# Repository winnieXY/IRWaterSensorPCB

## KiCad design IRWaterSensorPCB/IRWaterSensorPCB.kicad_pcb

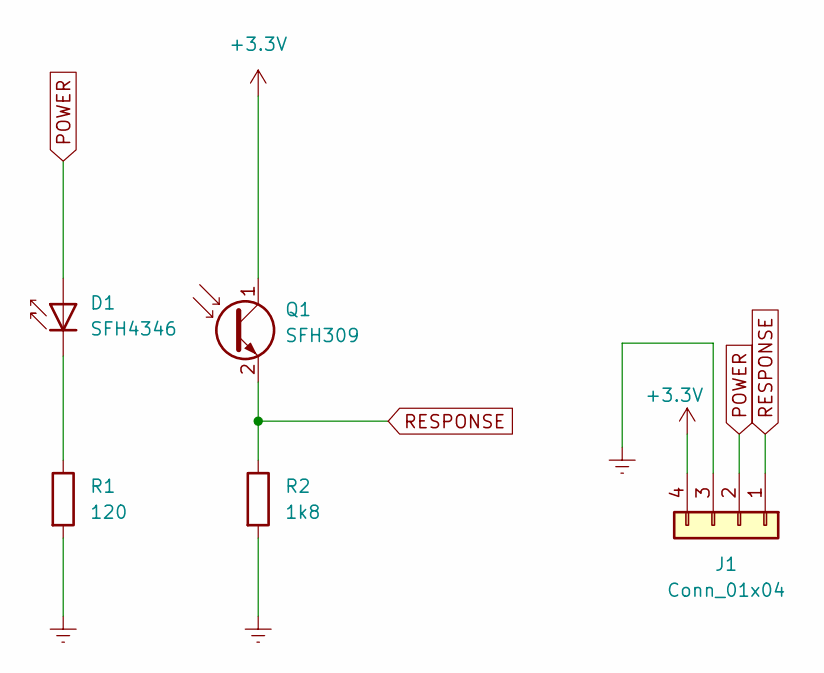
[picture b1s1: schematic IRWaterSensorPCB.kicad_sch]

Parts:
D1: SFH4346; LED_D3.0mm_IRBlack
J1: Conn_01x04; JST_XH_B4B-XH-A_1x04_P2.50mm_Vertical
Q1: SFH309; LED_D3.0mm_Clear
R1: 120; R_1206_3216Metric_Pad1.30x1.75mm_HandSolder
R2: 1k8; R_1206_3216Metric_Pad1.30x1.75mm_HandSolder

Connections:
+3V3: J1.4, Q1.1 (C)
Earth: J1.3, R1.2, R2.2
unnamed: D1.1 (K), R1.1
POWER: D1.2 (A), J1.2
RESPONSE: J1.1, Q1.2 (E), R2.1

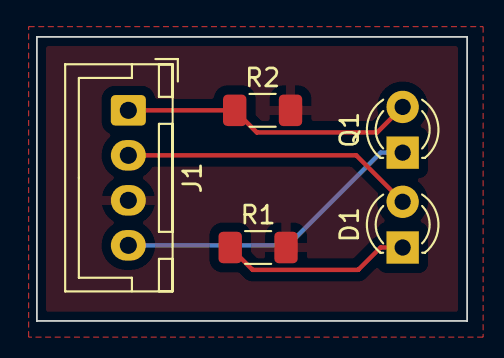
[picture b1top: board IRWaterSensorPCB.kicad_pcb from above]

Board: 2 copper layers, 23.9 x 15.8 mm, 5 parts (0 on the bottom side), 5 nets.
